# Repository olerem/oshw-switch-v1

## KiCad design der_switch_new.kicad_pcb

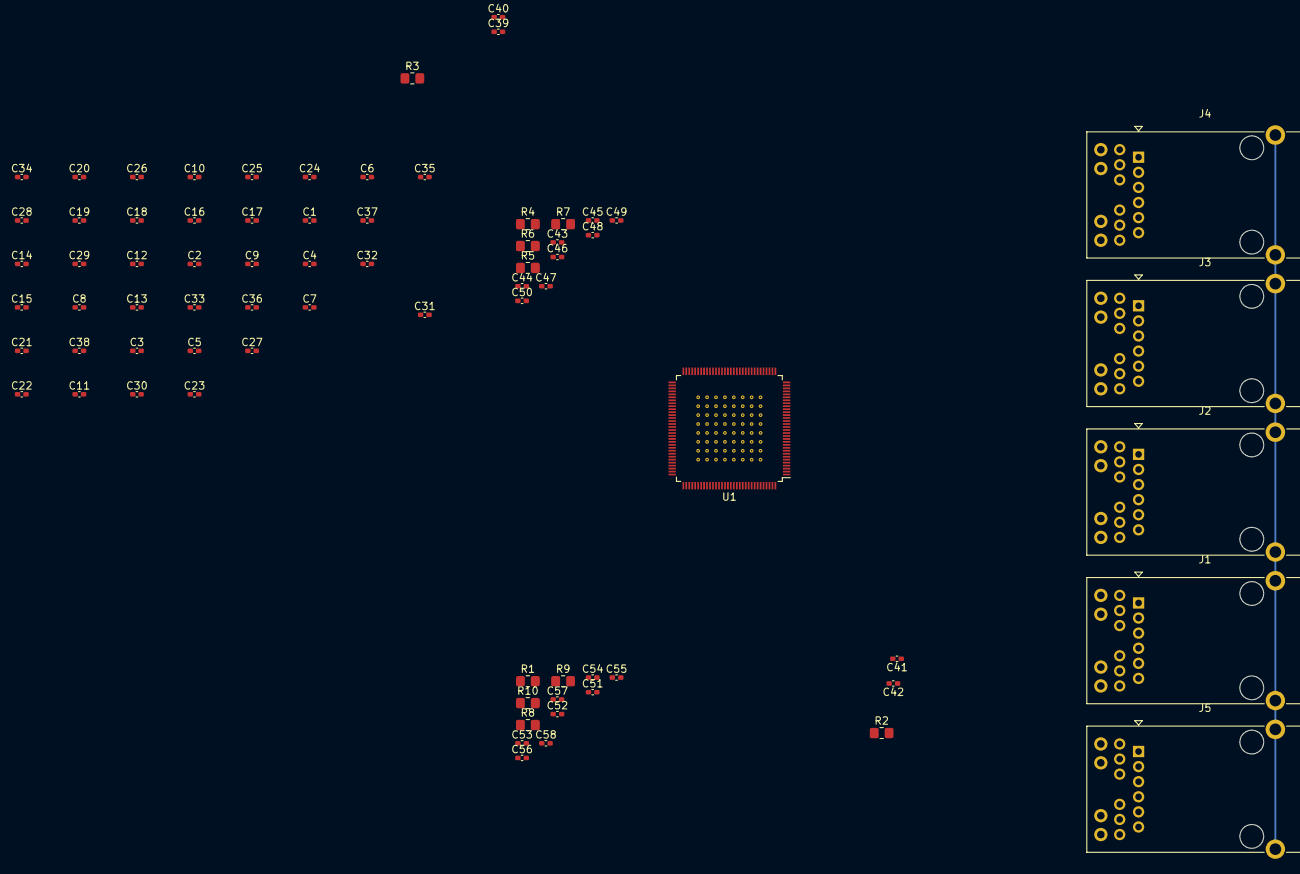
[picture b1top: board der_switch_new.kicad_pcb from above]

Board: 6 copper layers, 74 parts (0 on the bottom side), 85 nets.

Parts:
C1, C2, C15, C30, C38: 22 uF; C_0402_1005Metric_Pad0.74x0.62mm_HandSolder
C3, C4, C5, C6, C7, C8, C9, C10, C11, C12, C13, C14, C16, C17, C18, C19, C20, C21, C22, C23, C24, C25, C26, C27, C28, C29, C31, C32, C33, C34, C36, C37, C39, C40, C41, C42, C43, C44, C45, C46, C47, C48, C49, C50, C51, C52, C53, C54, C55, C56, C57, C58: 0.1 uF; C_0402_1005Metric_Pad0.74x0.62mm_HandSolder
C35: 10 uF; C_0402_1005Metric_Pad0.74x0.62mm_HandSolder
J1, J2, J3, J4, J5: JK0654219; RJ45_Pulse_JK0654219NL_Horizontal
R1, R2, R3, R4, R5, R6, R7, R8, R9, R10: 330; R_0805_2012Metric_Pad1.20x1.40mm_HandSolder
U1: KSZ9477S; TQFP-128_14x14mm_P0.4mm_EP10x10mm_ThermalVias

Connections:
+1V2: C1.1, C2.1, C3.1, C4.1, C5.1, C6.1, C7.1, C8.1, C9.1, C10.1, C11.1, C12.1, C13.1, C14.1, C15.1, C16.1, C17.1, C18.1, C19.1, C20.1, C21.1, C22.1, C23.1, U1.3 (AVDDL), U1.11 (DVDDL), U1.14 (AVDDL), U1.19 (AVDDL), U1.23 (DVDDL), U1.30 (AVDDL), U1.36 (AVDDL), U1.41 (AVDDL), U1.45 (DVDDL), U1.56 (DVDDL), U1.66 (DVDDL), U1.70 (DVDDL), U1.71 (VDDLS), U1.84 (VDDLS), U1.87 (DVDDL), U1.104 (DVDDL), U1.110 (DVDDL), U1.114 (AVDDL), U1.119 (AVDDL), U1.124 (AVDDL)
+2V5: C24.1, C25.1, C26.1, C27.1, C29.1, C30.1, C32.1, C34.1, C36.1, C37.1, C38.1, U1.10 (AVDDH), U1.22 (AVDDH), U1.33 (AVDDH), U1.44 (AVDDH), U1.72 (VDDHS), U1.83 (VDDHS), U1.111 (AVDDH), U1.122 (AVDDH), U1.128 (AVDDH)
+3V3: C28.1, C31.1, C33.1, C35.1, R1.1, R2.1, R3.1, R4.1, R5.1, R6.1, R7.1, R8.1, R9.1, R10.1, U1.61 (VDDIO), U1.68 (VDDIO), U1.99 (VDDIO)
/ethernet ports/P5_A_M: J5.10 (MX1-), U1.113 (TXRX5M_A)
/ethernet ports/P5_A_P: J5.11 (MX1+), U1.112 (TXRX5P_A)
/ethernet ports/P5_B_M: J5.5 (MX2-), U1.116 (TXRX5M_B)
/ethernet ports/P5_B_P: J5.4 (MX2+), U1.115 (TXRX5P_B)
/ethernet ports/P5_C_M: J5.2 (MX3-), U1.118 (TXRX5M_C)
/ethernet ports/P5_C_P: J5.3 (MX3+), U1.117 (TXRX5P_C)
/ethernet ports/P5_D_M: J5.9 (MX4-), U1.121 (TXRX5M_D)
/ethernet ports/P5_D_P: J5.8 (MX4+), U1.120 (TXRX5P_D)
/ethernet ports/P5_LED0: J5.15 (LED1-), U1.102 (LED5_0)
/ethernet ports/P5_LED1: J5.13 (LED2-), U1.103 (LED5_1)
/ethernet ports/ethernet_ports_1_2/P1_A_M: J1.10 (MX1-), U1.2 (TXRX1M_A)
/ethernet ports/ethernet_ports_1_2/P1_A_P: J1.11 (MX1+), U1.1 (TXRX1P_A)
/ethernet ports/ethernet_ports_1_2/P1_B_M: J1.5 (MX2-), U1.5 (TXRX1M_B)
/ethernet ports/ethernet_ports_1_2/P1_B_P: J1.4 (MX2+), U1.4 (TXRX1P_B)
/ethernet ports/ethernet_ports_1_2/P1_C_M: J1.2 (MX3-), U1.7 (TXRX1M_C)
/ethernet ports/ethernet_ports_1_2/P1_C_P: J1.3 (MX3+), U1.6 (TXRX1P_C)
/ethernet ports/ethernet_ports_1_2/P1_D_M: J1.9 (MX4-), U1.9 (TXRX1M_D)
/ethernet ports/ethernet_ports_1_2/P1_D_P: J1.8 (MX4+), U1.8 (TXRX1P_D)
/ethernet ports/ethernet_ports_1_2/P1_LED0: J1.15 (LED1-), U1.105 (LED1_0)
/ethernet ports/ethernet_ports_1_2/P1_LED1: J1.13 (LED2-), U1.106 (LED1_1)
/ethernet ports/ethernet_ports_1_2/P2_A_M: J2.10 (MX1-), U1.13 (TXRX2M_A)
/ethernet ports/ethernet_ports_1_2/P2_A_P: J2.11 (MX1+), U1.12 (TXRX2P_A)
/ethernet ports/ethernet_ports_1_2/P2_B_M: J2.5 (MX2-), U1.16 (TXRX2M_B)
/ethernet ports/ethernet_ports_1_2/P2_B_P: J2.4 (MX2+), U1.15 (TXRX2P_B)
/ethernet ports/ethernet_ports_1_2/P2_C_M: J2.2 (MX3-), U1.18 (TXRX2M_C)
/ethernet ports/ethernet_ports_1_2/P2_C_P: J2.3 (MX3+), U1.17 (TXRX2P_C)
/ethernet ports/ethernet_ports_1_2/P2_D_M: J2.9 (MX4-), U1.21 (TXRX2M_D)
/ethernet ports/ethernet_ports_1_2/P2_D_P: J2.8 (MX4+), U1.20 (TXRX2P_D)
/ethernet ports/ethernet_ports_1_2/P2_LED0: J2.15 (LED1-), U1.91 (LED2_0)
/ethernet ports/ethernet_ports_1_2/P2_LED1: J2.13 (LED2-), U1.92 (LED2_1)
/ethernet ports/ethernet_ports_3_4/P3_A_M: J3.10 (MX1-), U1.25 (TXRX3M_A)
/ethernet ports/ethernet_ports_3_4/P3_A_P: J3.11 (MX1+), U1.24 (TXRX3P_A)
/ethernet ports/ethernet_ports_3_4/P3_B_M: J3.5 (MX2-), U1.27 (TXRX3M_B)
/ethernet ports/ethernet_ports_3_4/P3_B_P: J3.4 (MX2+), U1.26 (TXRX3P_B)
/ethernet ports/ethernet_ports_3_4/P3_C_M: J3.2 (MX3-), U1.29 (TXRX3M_C)
/ethernet ports/ethernet_ports_3_4/P3_C_P: J3.3 (MX3+), U1.28 (TXRX3P_C)
/ethernet ports/ethernet_ports_3_4/P3_D_M: J3.9 (MX4-), U1.32 (TXRX3M_D)
/ethernet ports/ethernet_ports_3_4/P3_D_P: J3.8 (MX4+), U1.31 (TXRX3P_D)
/ethernet ports/ethernet_ports_3_4/P3_LED0: J3.15 (LED1-), U1.88 (LED3_0)
/ethernet ports/ethernet_ports_3_4/P3_LED1: J3.13 (LED2-), U1.89 (LED3_1)
/ethernet ports/ethernet_ports_3_4/P4_A_M: J4.10 (MX1-), U1.35 (TXRX4M_A)
/ethernet ports/ethernet_ports_3_4/P4_A_P: J4.11 (MX1+), U1.34 (TXRX4P_A)
/ethernet ports/ethernet_ports_3_4/P4_B_M: J4.5 (MX2-), U1.38 (TXRX4M_B)
/ethernet ports/ethernet_ports_3_4/P4_B_P: J4.4 (MX2+), U1.37 (TXRX4P_B)
/ethernet ports/ethernet_ports_3_4/P4_C_M: J4.2 (MX3-), U1.40 (TXRX4M_C)
/ethernet ports/ethernet_ports_3_4/P4_C_P: J4.3 (MX3+), U1.39 (TXRX4P_C)
/ethernet ports/ethernet_ports_3_4/P4_D_M: J4.9 (MX4-), U1.43 (TXRX4M_D)
/ethernet ports/ethernet_ports_3_4/P4_D_P: J4.8 (MX4+), U1.42 (TXRX4P_D)
/ethernet ports/ethernet_ports_3_4/P4_LED0: J4.15 (LED1-), U1.85 (LED4_0)
/ethernet ports/ethernet_ports_3_4/P4_LED1: J4.13 (LED2-), U1.86 (LED4_1)
Earth: J1.SH, J2.SH, J3.SH, J4.SH, J5.SH
GND: C1.2, C2.2, C3.2, C4.2, C5.2, C6.2, C7.2, C8.2, C9.2, C10.2, C11.2, C12.2, C13.2, C14.2, C15.2, C16.2, C17.2, C18.2, C19.2, C20.2, C21.2, C22.2, C23.2, C24.2, C25.2, C26.2, C27.2, C28.2, C29.2, C30.2, C31.2, C32.2, C33.2, C34.2, C35.2, C36.2, C37.2, C38.2, C39.2, C40.2, C41.2, C42.2, C43.2, C44.2, C45.2, C46.2, C47.2, C48.2, C49.2, C50.2, C51.2, C52.2, C53.2, C54.2, C55.2, C56.2, C57.2, C58.2, U1.46 (GND), U1.47 (GND), U1.69 (GND), U1.75 (GND), U1.77 (GND), U1.80 (GND), U1.107 (GND), U1.109 (GND), U1.123 (GND), U1.129 (PAD)
unnamed: C39.1, J5.12 (MXCT1)
unnamed: C40.1, J5.6 (MXCT2)
unnamed: C41.1, J5.1 (MXCT3)
unnamed: C42.1, J5.7 (MXCT4)
unnamed: C43.1, J1.12 (MXCT1)
unnamed: C44.1, J1.6 (MXCT2)
unnamed: C45.1, J1.1 (MXCT3)
unnamed: C46.1, J1.7 (MXCT4)
unnamed: C47.1, J2.12 (MXCT1)
unnamed: C48.1, J2.6 (MXCT2)
unnamed: C49.1, J2.1 (MXCT3)
unnamed: C50.1, J2.7 (MXCT4)
unnamed: C51.1, J3.12 (MXCT1)
unnamed: C52.1, J3.6 (MXCT2)
unnamed: C53.1, J3.1 (MXCT3)
unnamed: C54.1, J3.7 (MXCT4)
unnamed: C55.1, J4.12 (MXCT1)
unnamed: C56.1, J4.6 (MXCT2)
unnamed: C57.1, J4.1 (MXCT3)
unnamed: C58.1, J4.7 (MXCT4)
unnamed: J1.14 (LED2+), R4.2
unnamed: J1.16 (LED1+), R6.2
unnamed: J2.14 (LED2+), R5.2
unnamed: J2.16 (LED1+), R7.2
unnamed: J3.14 (LED2+), R8.2
unnamed: J3.16 (LED1+), R10.2
unnamed: J4.14 (LED2+), R9.2
unnamed: J4.16 (LED1+), R1.2
unnamed: J5.14 (LED2+), R2.2
unnamed: J5.16 (LED1+), R3.2

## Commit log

2021-01-19 ksz9477s: add NC pincs
2021-01-19 ksz9477s: move around some anotations
2021-01-20 Add power supply to the KSZ9477S
2021-01-20 ksz9477s: update location for anotations
2021-01-21 add ports
2021-01-22 add TQFP-128_14x14mm_P0.4mm_EP10x10mm_ThermalVias footprint
    and assign it to the ksz chip
2021-01-31 update pin naming. use _P/_N to allow optiomisation for differential signal
